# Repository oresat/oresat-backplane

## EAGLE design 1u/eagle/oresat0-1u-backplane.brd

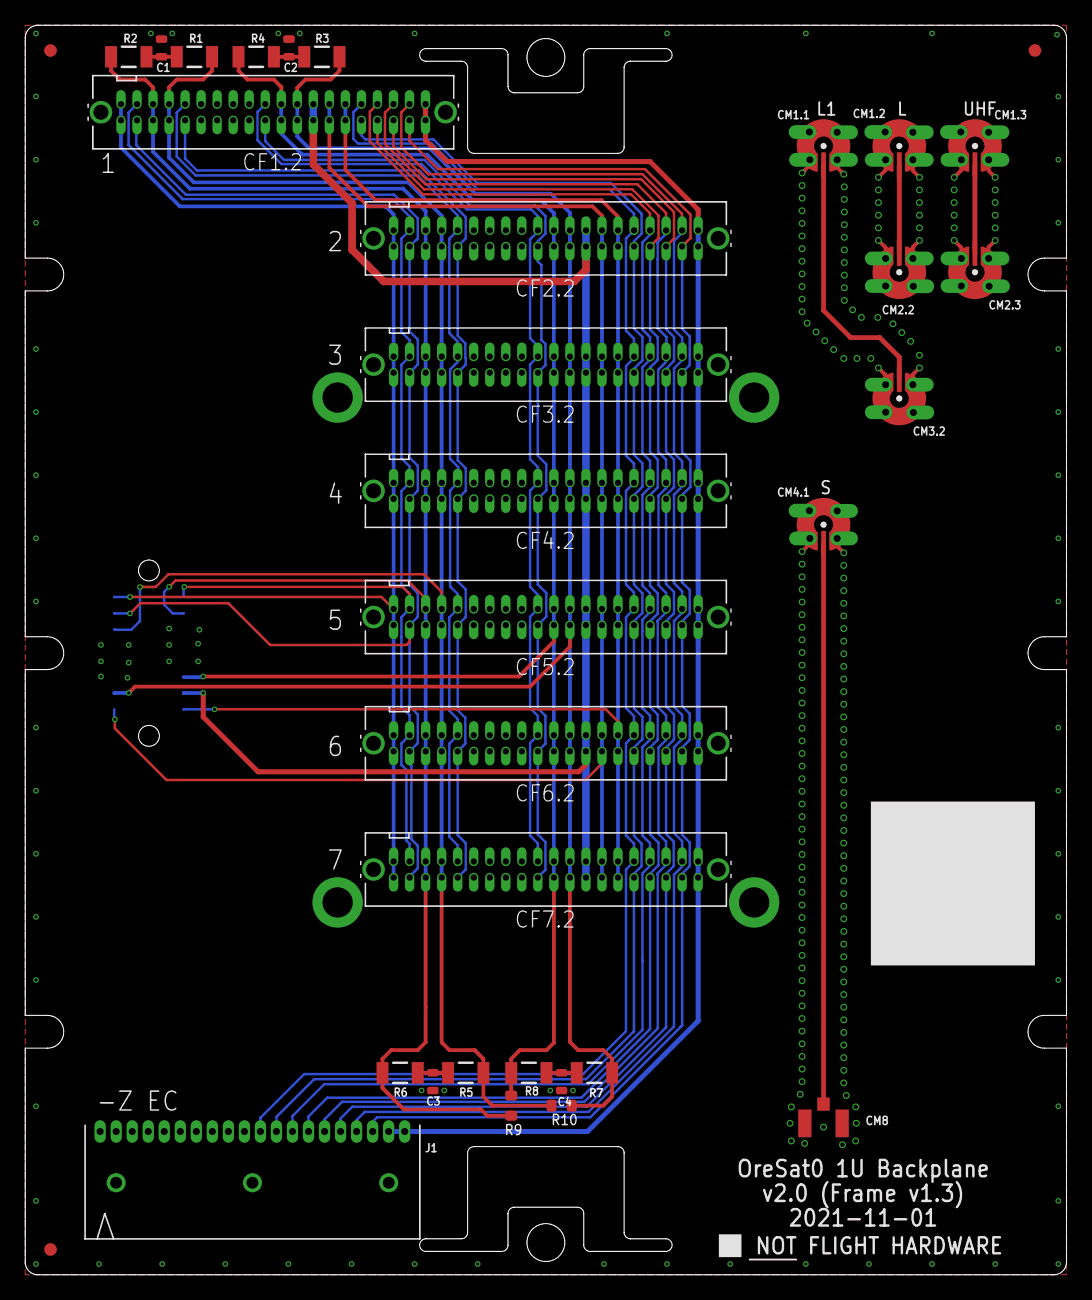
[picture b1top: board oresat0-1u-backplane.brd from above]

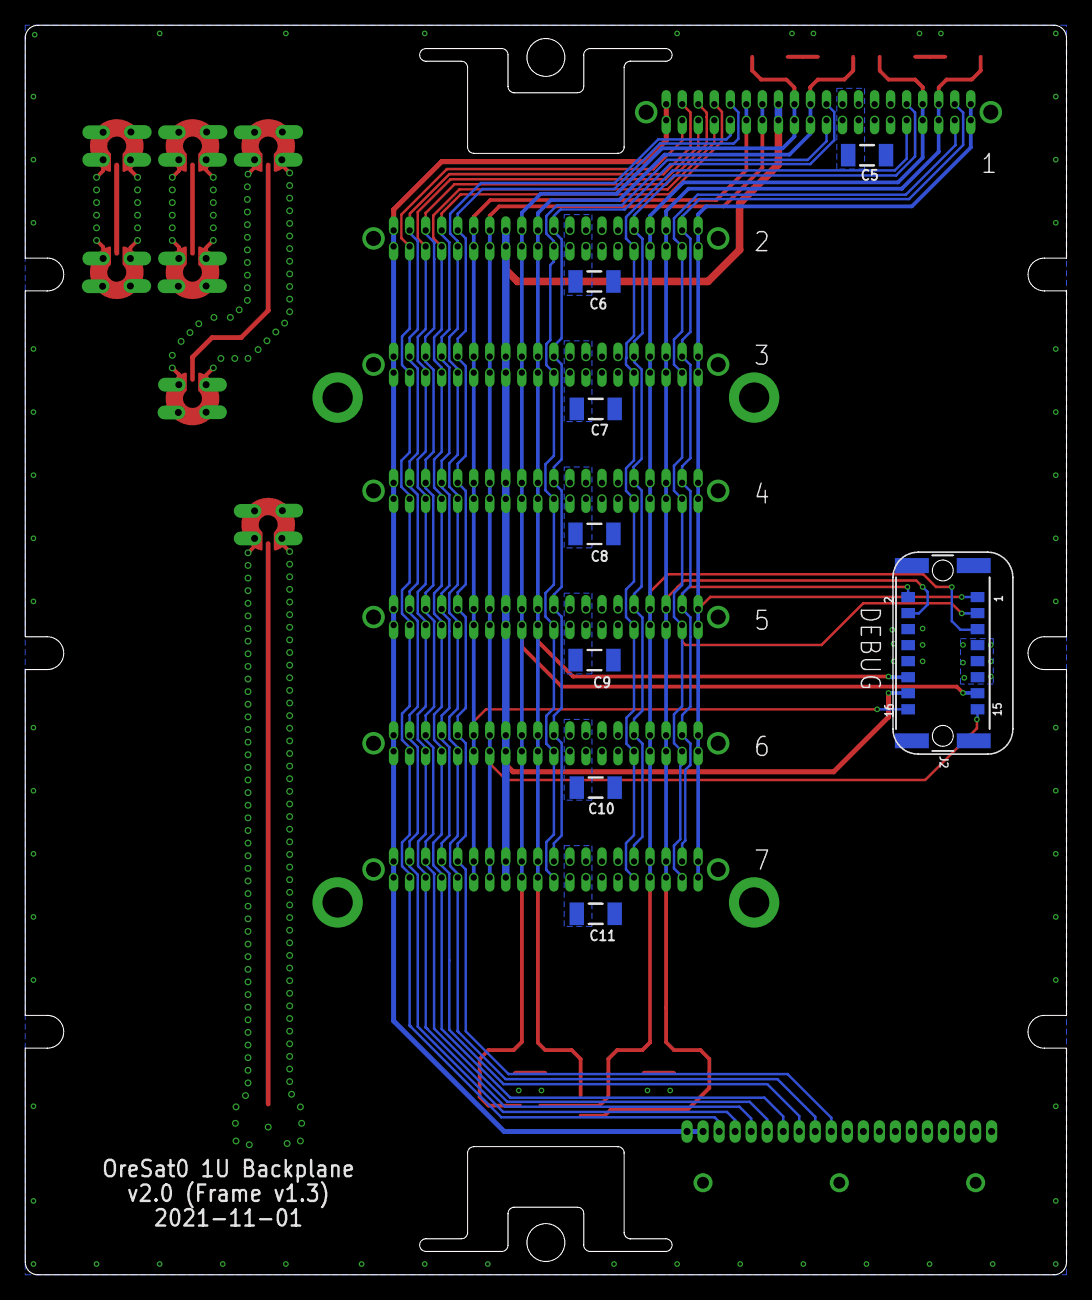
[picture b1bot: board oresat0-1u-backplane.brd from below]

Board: 4 copper layers, 82.5 x 99.0 mm, 42 parts (8 on the bottom side), 33 nets.

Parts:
C1, C2, C3, C4: 1n; .0603-C-NOSILK
C5, C6, C7, C8, C9, C10, C11: 10u 25V; 1206-B
CF1.2, CF2.2, CF3.2, CF4.2, CF5.2, CF6.2, CF7.2: SFM-120-X1-XXX-D
CM1.1, CM1.2, CM1.3, CM2.2, CM2.3, CM3.2, CM4.1: J-MOLEX-SMPM-73300-0111X
CM8: U.FL-R-SMA; U.FL-R-SMT
FIDUCIAL1, FIDUCIAL2, FIDUCIAL3: FIDUCIAL-1.0X2.0
J1: 5-104196-5
J2: M55-6001642R; CONN_M55-6001642R_HRW
R1, R2, R3, R4: 60.4; 1206-C
R5, R6, R7, R8: NP/60.4; 1206-C
R9, R10: 0; .0603-B-NOSILK
U$1: FLIGHMARKERNEW; FLIGHTMARKER_NEW_BOARDS

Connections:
!SD: CF1.2.39, CF1.2.40, CF2.2.39, CF2.2.40, CF3.2.39, CF3.2.40, CF4.2.39, CF4.2.40, CF5.2.39, CF5.2.40, CF6.2.39, CF6.2.40, CF7.2.39, CF7.2.40, J2.1
C3-UART-RX: CF1.2.38, CF2.2.38, CF3.2.38, CF4.2.38, CF5.2.38, CF6.2.38, CF7.2.38, J2.2
C3-UART-TX: CF1.2.37, CF2.2.37, CF3.2.37, CF4.2.37, CF5.2.37, CF6.2.37, CF7.2.37, J2.3
CAN1_H: CF1.2.33, CF1.2.34, CF2.2.33, CF2.2.34, CF3.2.33, CF3.2.34, CF4.2.33, CF4.2.34, CF5.2.33, CF5.2.34, CF6.2.33, CF6.2.34, CF7.2.33, CF7.2.34, J2.5, R1.1, R5.1, R10.1
CAN1_L: CF1.2.35, CF1.2.36, CF2.2.35, CF2.2.36, CF3.2.35, CF3.2.36, CF4.2.35, CF4.2.36, CF5.2.35, CF5.2.36, CF6.2.35, CF6.2.36, CF7.2.35, CF7.2.36, J2.4, R2.1, R6.1, R9.1
CAN2_H: CF1.2.17, CF1.2.18, CF2.2.17, CF2.2.18, CF3.2.17, CF3.2.18, CF4.2.17, CF4.2.18, CF5.2.17, CF5.2.18, CF6.2.17, CF6.2.18, CF7.2.17, CF7.2.18, J2.13, R3.1, R7.1, R10.2
CAN2_L: CF1.2.19, CF1.2.20, CF2.2.19, CF2.2.20, CF3.2.19, CF3.2.20, CF4.2.19, CF4.2.20, CF5.2.19, CF5.2.20, CF6.2.19, CF6.2.20, CF7.2.19, CF7.2.20, J2.12, R4.1, R8.1, R9.2
GND: C1.2, C2.2, C3.2, C4.2, C5.2, C6.2, C7.2, C8.2, C9.2, C10.2, C11.2, CF1.2.27, CF1.2.28, CF1.2.29, CF1.2.30, CF1.2.LC1, CF1.2.LC2, CF2.2.27, CF2.2.28, CF2.2.29, CF2.2.30, CF2.2.LC1, CF2.2.LC2, CF3.2.27, CF3.2.28, CF3.2.29, CF3.2.30, CF3.2.LC1, CF3.2.LC2, CF4.2.27, CF4.2.28, CF4.2.29, CF4.2.30, CF4.2.LC1, CF4.2.LC2, CF5.2.27, CF5.2.28, CF5.2.29, CF5.2.30, CF5.2.LC1, CF5.2.LC2, CF6.2.27, CF6.2.28, CF6.2.29, CF6.2.30, CF6.2.LC1, CF6.2.LC2, CF7.2.27, CF7.2.28, CF7.2.29, CF7.2.30, CF7.2.LC1, CF7.2.LC2, CM1.1.P$1, CM1.1.P$2, CM1.1.P$3, CM1.1.P$4, CM1.2.P$1, CM1.2.P$2, CM1.2.P$3, CM1.2.P$4, CM1.3.P$1, CM1.3.P$2, CM1.3.P$3, CM1.3.P$4, CM2.2.P$1, CM2.2.P$2, CM2.2.P$3, CM2.2.P$4, CM2.3.P$1, CM2.3.P$2, CM2.3.P$3, CM2.3.P$4, CM3.2.P$1, CM3.2.P$2, CM3.2.P$3, CM3.2.P$4, CM4.1.P$1, CM4.1.P$2, CM4.1.P$3, CM4.1.P$4, CM8.2, CM8.3, J1.HD1, J1.HD2, J1.HD3, J2.6, J2.8, J2.10, J2.19, J2.20, J2.21, J2.22
L1-TURNSTILE: CM1.1.RF-DOWN, CM3.2.RF-DOWN
L-TURNSTILE: CM1.2.RF-DOWN, CM2.2.RF-DOWN
unnamed: C2.1, R3.2, R4.2
unnamed: C1.1, R1.2, R2.2
unnamed: C4.1, R7.2, R8.2
unnamed: C3.1, R5.2, R6.2
OPD_PWR: CF1.2.15, CF1.2.16, CF2.2.15, CF2.2.16, CF3.2.15, CF3.2.16, CF4.2.15, CF4.2.16, CF5.2.15, CF5.2.16, CF6.2.15, CF6.2.16, CF7.2.15, CF7.2.16, J2.14
OPD_SCL: CF1.2.13, CF1.2.14, CF2.2.13, CF2.2.14, CF3.2.13, CF3.2.14, CF4.2.13, CF4.2.14, CF5.2.13, CF5.2.14, CF6.2.13, CF6.2.14, CF7.2.13, CF7.2.14, J2.15
OPD_SDA: CF1.2.11, CF1.2.12, CF2.2.11, CF2.2.12, CF3.2.11, CF3.2.12, CF4.2.11, CF4.2.12, CF5.2.11, CF5.2.12, CF6.2.11, CF6.2.12, CF7.2.11, CF7.2.12, J2.16
S-PATCH: CM4.1.RF-DOWN, CM8.1
SPARE1-MAG-SDA: CF1.2.1, CF1.2.2, CF2.2.1, CF2.2.2, CF3.2.1, CF3.2.2, CF4.2.1, CF4.2.2, CF5.2.1, CF5.2.2, CF6.2.1, CF6.2.2, CF7.2.1, CF7.2.2, J1.19, J1.20
SPARE3-MAG-SCL: CF1.2.3, CF2.2.3, CF3.2.3, CF4.2.3, CF5.2.3, CF6.2.3, CF7.2.3, J1.18
SPARE4-MAG-SCL: CF1.2.4, CF2.2.4, CF3.2.4, CF4.2.4, CF5.2.4, CF6.2.4, CF7.2.4, J1.17
SPARE5-MAG-POWER: CF1.2.5, CF2.2.5, CF3.2.5, CF4.2.5, CF5.2.5, CF6.2.5, CF7.2.5, J1.16
SPARE6-MAG-POWER: CF1.2.6, CF2.2.6, CF3.2.6, CF4.2.6, CF5.2.6, CF6.2.6, CF7.2.6, J1.15
SPARE7: CF1.2.7, CF2.2.7, CF3.2.7, CF4.2.7, CF5.2.7, CF6.2.7, CF7.2.7, J1.14
SPARE8: CF1.2.8, CF2.2.8, CF3.2.8, CF4.2.8, CF5.2.8, CF6.2.8, CF7.2.8, J1.13
SPARE9-TURNSTILE-DEPLOY: CF1.2.9, CF2.2.9, CF3.2.9, CF4.2.9, CF5.2.9, CF6.2.9, CF7.2.9, J1.12
SPARE10-TURNSTILE-DEPLOY: CF1.2.10, CF2.2.10, CF3.2.10, CF4.2.10, CF5.2.10, CF6.2.10, CF7.2.10, J1.11
SPARE21: CF1.2.21, CF2.2.21, CF3.2.21, CF4.2.21, CF5.2.21, CF6.2.21, CF7.2.21
SPARE22: CF1.2.22, CF2.2.22, CF3.2.22, CF4.2.22, CF5.2.22, CF6.2.22, CF7.2.22
SPARE31: CF1.2.31, CF2.2.31, CF3.2.31, CF4.2.31, CF5.2.31, CF6.2.31, CF7.2.31
SPARE32: CF1.2.32, CF2.2.32, CF3.2.32, CF4.2.32, CF5.2.32, CF6.2.32, CF7.2.32
UHF-TURNSTILE: CM1.3.RF-DOWN, CM2.3.RF-DOWN
VBUS: C5.1, C6.1, C7.1, C8.1, C9.1, C10.1, C11.1, CF1.2.23, CF1.2.24, CF1.2.25, CF1.2.26, CF2.2.23, CF2.2.24, CF2.2.25, CF2.2.26, CF3.2.23, CF3.2.24, CF3.2.25, CF3.2.26, CF4.2.23, CF4.2.24, CF4.2.25, CF4.2.26, CF5.2.23, CF5.2.24, CF5.2.25, CF5.2.26, CF6.2.23, CF6.2.24, CF6.2.25, CF6.2.26, CF7.2.23, CF7.2.24, CF7.2.25, CF7.2.26, J2.7, J2.9, J2.11

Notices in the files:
parts and their libraries:
COPYRIGHT: Copyright (C) 2021 Ultra Librarian. All rights reserved.
